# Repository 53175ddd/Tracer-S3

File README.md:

# 基板概要

JLCPCB の PCBA に対応した，私 [MOS](https://x.com/53175ddd) 作成のオリジナルライントレーサです  
表面実装部品（ESP32-S3 モジュール・SMD 抵抗・コンデンサ・レギュレータ・ダイオード）のみ PCBA で実装してくれるようにしています  
それ以外の部品については下記部品表を参考に，必要に応じて部品を変更するなどしてご利用ください

# イメージ

<div align="center">
  
</div>
<div align="center">
  
</div>

# 部品表

| 部品番号 | 定数 | 秋月 |
|----|----|----|
| R2 ~ R6 | 47Ω 1/4W | <https://akizukidenshi.com/catalog/g/g125470/> |
| R7 ~ R11 | 3.3kΩ ~ 4.7kΩ 1/4W | 省略 |
| SW1, SW2 | タクトスイッチ | <https://akizukidenshi.com/catalog/g/g103648/> |
| SW3 | DPDT スイッチ | <https://akizukidenshi.com/catalog/g/g102627/> |
| Q1 | MOSFET | <https://akizukidenshi.com/catalog/g/g107597/> |
| U3 | モータドライバ DRV8835 | <https://akizukidenshi.com/catalog/g/g109848/> |
| BZ1 | ブザー | <https://akizukidenshi.com/catalog/g/g104118/> |
| J1 | 1x6 ピンソケット | <https://akizukidenshi.com/catalog/g/g103784/> |
| J2, J3 | 2x2 ピンヘッダ | <https://akizukidenshi.com/catalog/g/g116792/> |
| J6 | 2x4 ピンヘッダ | <https://akizukidenshi.com/catalog/g/g116793/> |
| J7 | バッテリコネクタ | 使用するバッテリに合うものを使用してください |
| D1 ~ D3 | 5V 抵抗内蔵 LED | <https://akizukidenshi.com/catalog/g/g106247/> |
| S1 ~ S5 | フォトセンサ LBR-127HLD | <https://akizukidenshi.com/catalog/g/g104500/> |

# その他部品

- タミヤ ギアボックス
- Li-Po バッテリ（2S）など
- Stamp ISP

がそれぞれ必要になります

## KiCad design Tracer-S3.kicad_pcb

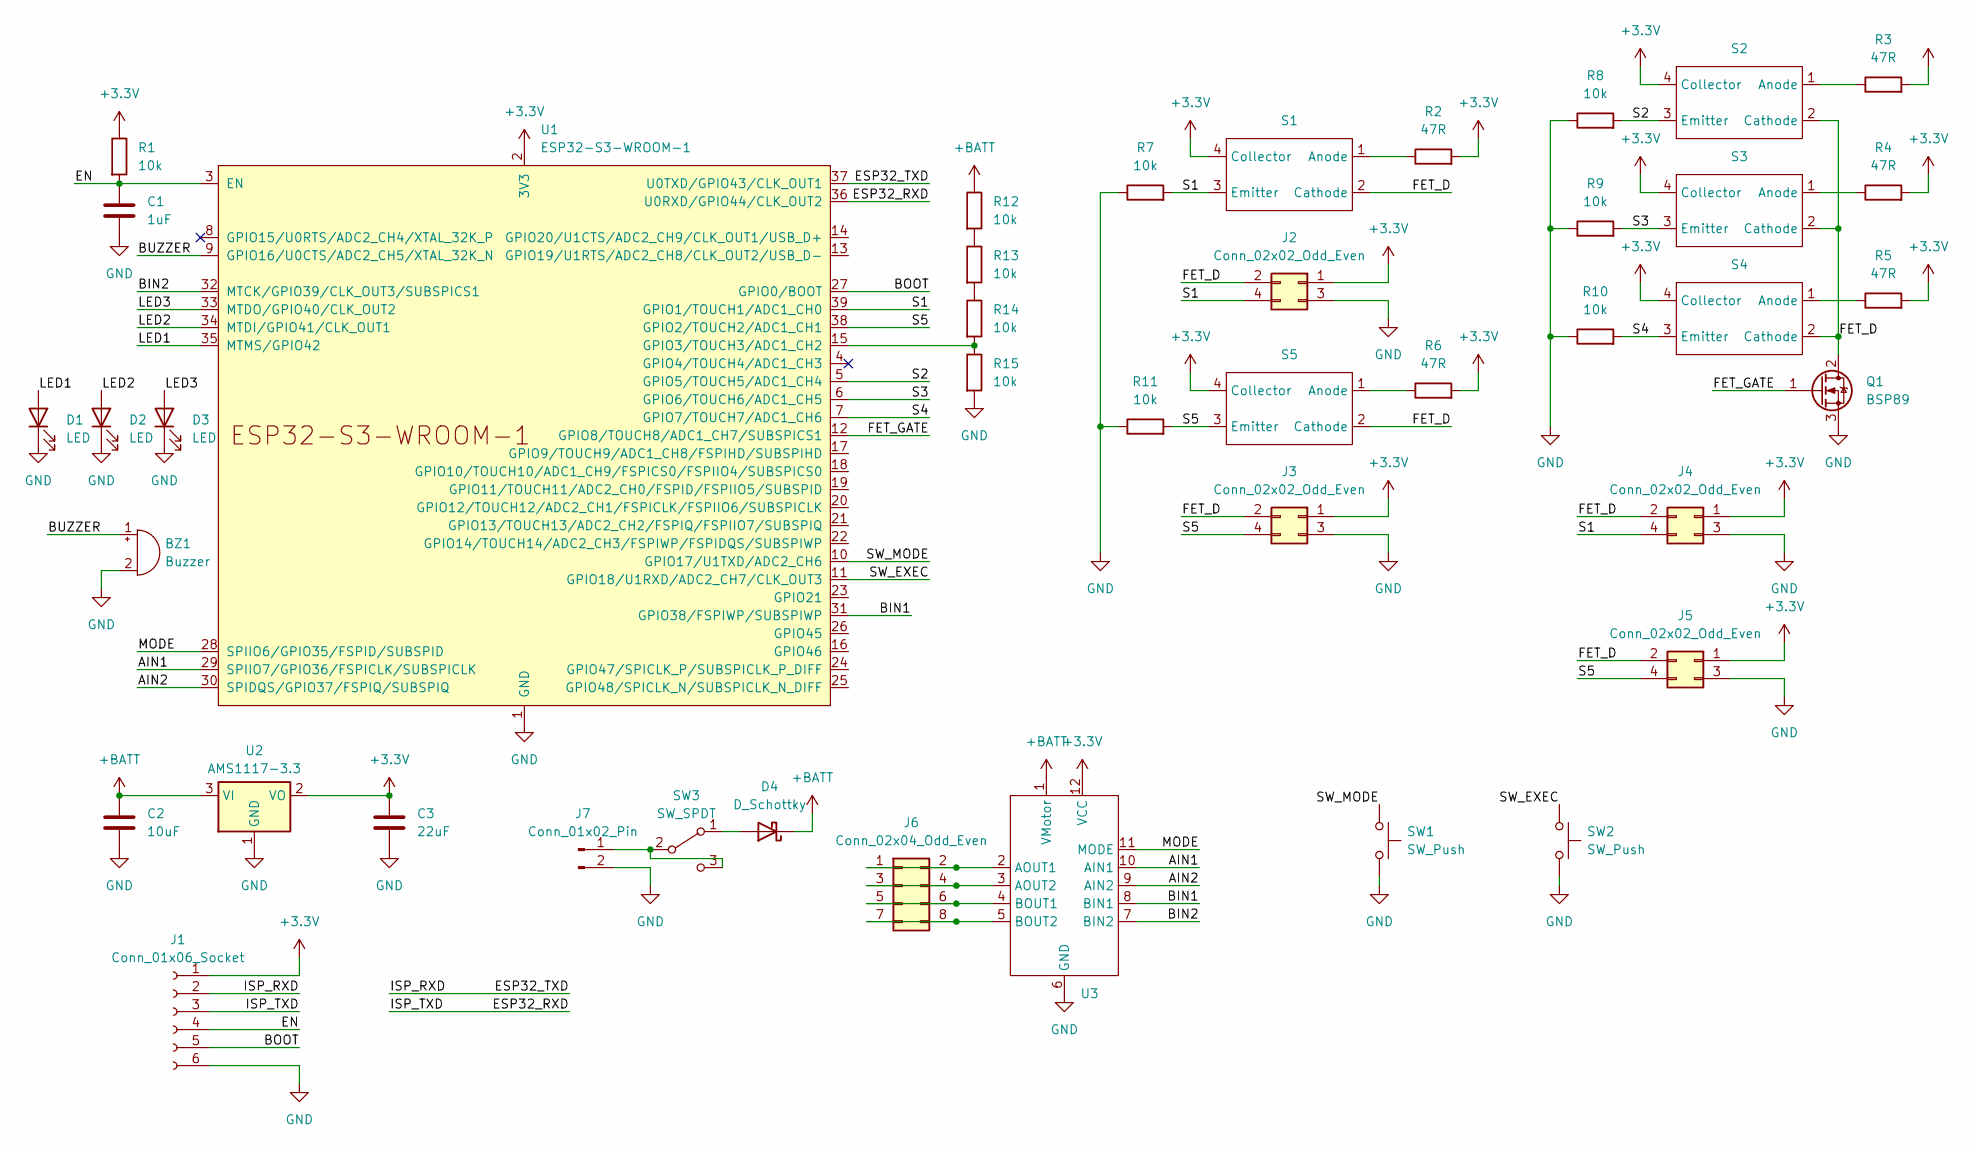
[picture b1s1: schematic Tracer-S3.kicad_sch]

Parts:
BZ1: Buzzer; Buzzer_TDK_PS1240P02BT_D12.2mm_H6.5mm
C1: 1uF; C_0603_1608Metric; LCSC C908011
C2: 10uF; C_0805_2012Metric; LCSC C162317
C3: 22uF; C_1210_3225Metric; LCSC C703078
D1, D2, D3: LED; LED_D5.0mm
D4: D_Schottky; D_SOD-123; LCSC C963381
J1: Conn_01x06_Socket; PinSocket_1x06_P2.54mm_Vertical
J2, J3, J4, J5: Conn_02x02_Odd_Even; PinSocket_2x02_P2.54mm_Vertical
J6: Conn_02x04_Odd_Even; PinSocket_2x04_P2.54mm_Vertical
J7: Conn_01x02_Pin; PinHeader_1x02_P2.54mm_Vertical
Q1: BSP89; TO-220-3_Vertical
R1, R12, R13, R14, R15: 10k; R_0603_1608Metric; LCSC C269701
R2, R3, R4, R5, R6: 47R; R_Axial_DIN0207_L6.3mm_D2.5mm_P10.16mm_Horizontal
R7, R8, R9, R10, R11: 10k; R_Axial_DIN0207_L6.3mm_D2.5mm_P10.16mm_Horizontal
S1, S2, S3, S4, S5: LBR-127HLD
SW1, SW2: SW_Push; SW_PUSH_6mm
SW3: SW_SPDT; SW_E-Switch_EG1271_SPDT
U1: ESP32-S3-WROOM-1
U2: AMS1117-3.3; SOT-223-3_TabPin2; LCSC C7432020
U3: AE-DRV8835

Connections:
+3.3V: C3.1, J1.1, J2.1, J3.1, J4.1, J5.1, R1.1, R2.2, R3.2, R4.2, R5.2, R6.2, S1.4 (Collector), S2.4 (Collector), S3.4 (Collector), S4.4 (Collector), S5.4 (Collector), U1.2 (3V3), U2.2 (VO), U3.12 (VCC)
+BATT: C2.1, D4.1 (K), R12.1, U2.3 (VI), U3.1 (VMotor)
/AIN1: U1.29 (SPIIO7/GPIO36/FSPICLK/SUBSPICLK), U3.10 (AIN1)
/AIN2: U1.30 (SPIDQS/GPIO37/FSPIQ/SUBSPIQ), U3.9 (AIN2)
/BIN1: U1.31 (GPIO38/FSPIWP/SUBSPIWP), U3.8 (BIN1)
/BIN2: U1.32 (MTCK/GPIO39/CLK_OUT3/SUBSPICS1), U3.7 (BIN2)
/BOOT: J1.5, U1.27 (GPIO0/BOOT)
/BUZZER: BZ1.1 (-), U1.9 (GPIO16/U0CTS/ADC2_CH5/XTAL_32K_N)
/EN: C1.1, J1.4, R1.2, U1.3 (EN)
/ESP32_RXD: J1.3, U1.36 (U0RXD/GPIO44/CLK_OUT2)
/ESP32_TXD: J1.2, U1.37 (U0TXD/GPIO43/CLK_OUT1)
/FET_D: J2.2, J3.2, J4.2, J5.2, Q1.2 (D), S1.2 (Cathode), S2.2 (Cathode), S3.2 (Cathode), S4.2 (Cathode), S5.2 (Cathode)
/FET_GATE: Q1.1 (G), U1.12 (GPIO8/TOUCH8/ADC1_CH7/SUBSPICS1)
/LED1: D1.2 (A), U1.35 (MTMS/GPIO42)
/LED2: D2.2 (A), U1.34 (MTDI/GPIO41/CLK_OUT1)
/LED3: D3.2 (A), U1.33 (MTDO/GPIO40/CLK_OUT2)
/MODE: U1.28 (SPIIO6/GPIO35/FSPID/SUBSPID), U3.11 (MODE)
/S1: J2.4, J4.4, R7.2, S1.3 (Emitter), U1.39 (GPIO1/TOUCH1/ADC1_CH0)
/S2: R8.2, S2.3 (Emitter), U1.5 (GPIO5/TOUCH5/ADC1_CH4)
/S3: R9.2, S3.3 (Emitter), U1.6 (GPIO6/TOUCH6/ADC1_CH5)
/S4: R10.2, S4.3 (Emitter), U1.7 (GPIO7/TOUCH7/ADC1_CH6)
/S5: J3.4, J5.4, R11.2, S5.3 (Emitter), U1.38 (GPIO2/TOUCH2/ADC1_CH1)
/SW_EXEC: SW2.1, U1.11 (GPIO18/U1RXD/ADC2_CH7/CLK_OUT3)
/SW_MODE: SW1.1, U1.10 (GPIO17/U1TXD/ADC2_CH6)
GND: BZ1.2 (+), C1.2, C2.2, C3.2, D1.1 (K), D2.1 (K), D3.1 (K), J1.6, J2.3, J3.3, J4.3, J5.3, J7.2, Q1.3 (S), R7.1, R8.1, R9.1, R10.1, R11.1, R15.2, SW1.2, SW2.2, U1.1 (GND), U1.40 (GND), U1.41 (GND), U2.1 (GND), U3.6 (GND)
unnamed: D4.2 (A), SW3.1 (A)
unnamed: J6.1, J6.2, U3.2 (AOUT1)
unnamed: J6.3, J6.4, U3.3 (AOUT2)
unnamed: J6.5, J6.6, U3.4 (BOUT1)
unnamed: J6.7, J6.8, U3.5 (BOUT2)
unnamed: J7.1, SW3.2 (B), SW3.3 (C)
unnamed: R12.2, R13.1
unnamed: R13.2, R14.1
unnamed: R2.1, S1.1 (Anode)
unnamed: R3.1, S2.1 (Anode)
unnamed: R4.1, S3.1 (Anode)
unnamed: R5.1, S4.1 (Anode)
unnamed: R6.1, S5.1 (Anode)
unnamed: R14.2, R15.1, U1.15 (GPIO3/TOUCH3/ADC1_CH2)

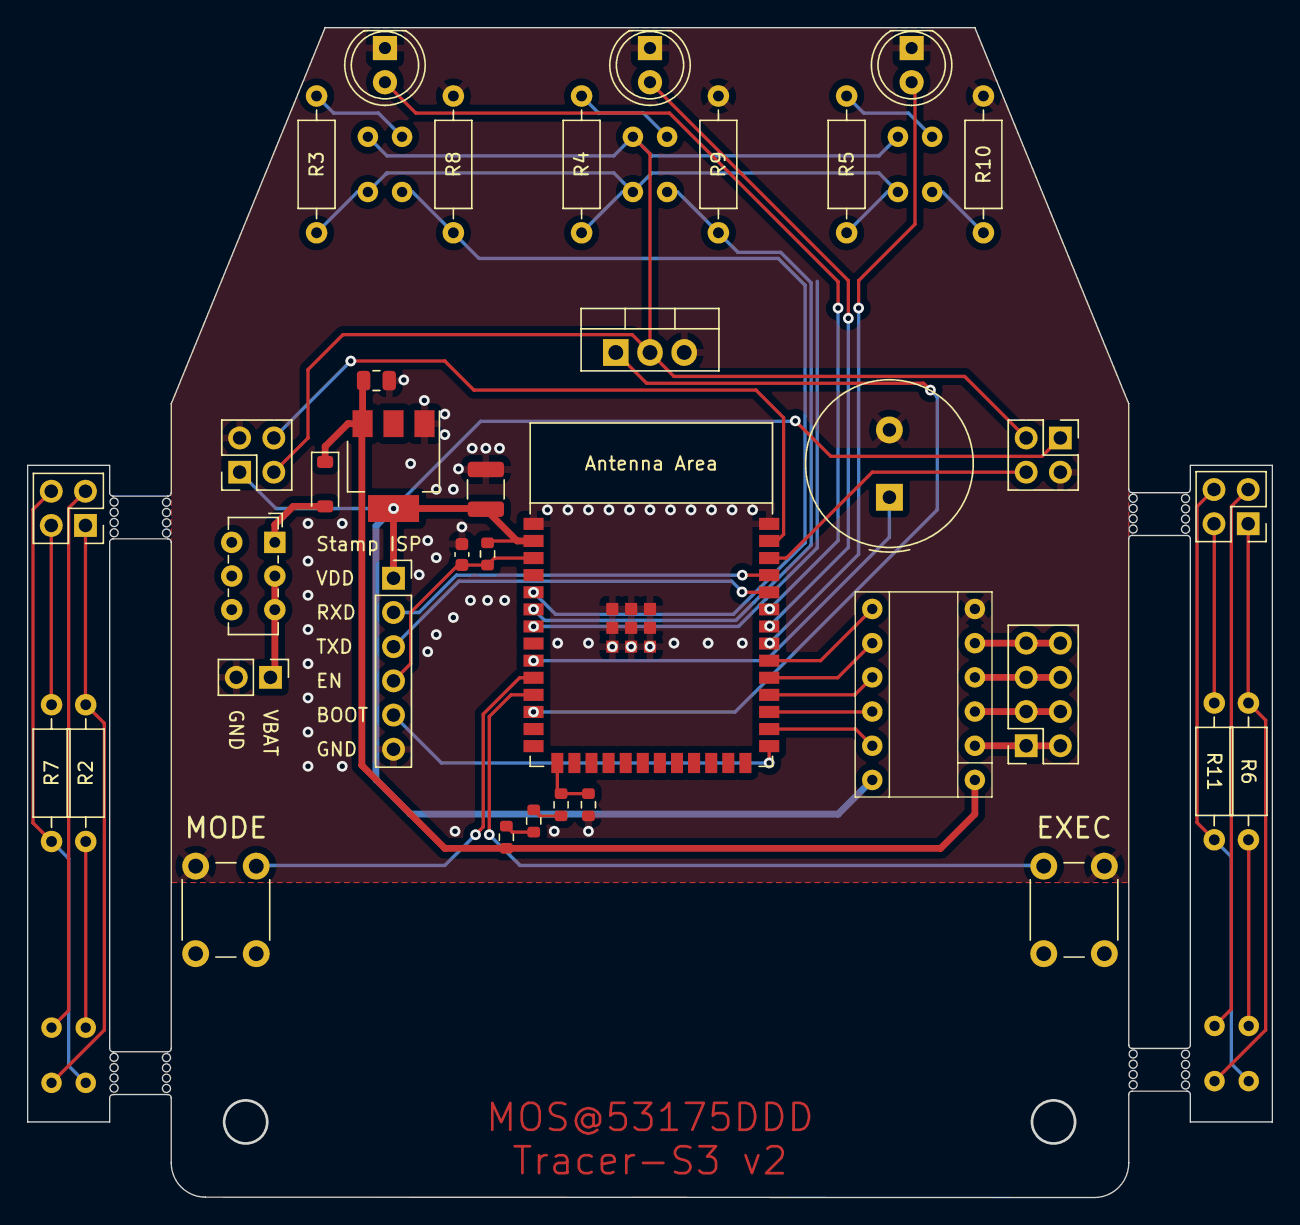
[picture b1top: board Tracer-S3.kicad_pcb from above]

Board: 2 copper layers, 92.4 x 86.8 mm, 42 parts (0 on the bottom side), 39 nets.

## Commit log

2024-06-13 部品定数修正
2024-06-13 部品番号修正
2024-06-14 部品変更
    フォトセンサの負荷抵抗を変更
    33k -> 10k
2024-06-18 回路定数変更
2024-06-21 センサ間隔調整・外形修正
2024-07-02 電源スイッチ配線変更・ミシン穴追加
2024-07-02 負荷抵抗変更
